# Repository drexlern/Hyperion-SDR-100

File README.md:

# Hyperion SDR-100

An open-source, homebrew **100W all-mode, all-band (160m–10m) HF Software-Defined Radio (SDR) transceiver** built around a **Xilinx Zynq SoC** architecture, an autonomous **7×7 L-network automatic antenna tuner (ATU)**, and a **60 FPS cross-platform desktop control head**.

---

## System Architecture

Hyperion SDR-100 is designed modularly so each RF, embedded, and software subsystem can be built, tested, and verified independently on the bench:

* **`/hardware-atu` — 100W 7×7 Automatic Antenna Tuner (KiCad):**
  * **Matching Network:** Binary-switched 7-inductor ($0.05\,\mu\text{H}$ – $4.5\,\mu\text{H}$ on Micrometals Type-2 powdered iron toroids) and 7-capacitor ($10\,\text{pF}$ – $1000\,\text{pF}$, $1\,\text{kV}$ C0G/NP0) L-network.
  * **Switching Matrix:** 16 Omron G2RL power relays ($14\times$ G2RL-1 SPDT for L/C banks, $1\times$ G2RL-2 DPDT for L/C topology reversal, $1\times$ G2RL-2 DPDT for full tuner bypass) driven via two daisy-chained **TI TPIC6B595N** open-drain shift registers.
  * **SWR & Power Sensing:** Built-in **Tandem Match (Stockton) directional coupler** wound on Fair-Rite BN43-202 binocular cores with 1N5711 Schottky peak detectors and $3.3\,\text{V}$ Zener ADC overvoltage protection.
  * **Controller:** **Seeed Studio XIAO ESP32-C3** mounted via through-hole headers for autonomous SWR tuning and USB/UART telemetry.
* **`/desktop-gui` — Shack Control Head (Python / Dear ImGui):**
  * 60 FPS OpenGL panadapter and 2D waterfall display powered by `imgui-bundle` (Dear ImGui + ImPlot) and `numpy`.
  * Live VFO tuning, band switching, real-time 16-relay ATU state visualizer, forward/reflected power & SWR metering, and a 180-second TX watchdog timer.
  * Designed for local Windows/Linux shack operation and low-latency remote streaming via **Parsec**.
* **`/firmware-esp32c3` — ATU Firmware (C++ / PlatformIO):** *(In Development)*
  * High-speed SPI shift-register control, ADC forward/reflected power sampling, and automated L/C impedance matching algorithms.
* **`/zynq-soc` — SDR Baseband & DSP (HDL / ARM C++):** *(Planned)*
  * Xilinx Zynq-7000 FPGA fabric for Digital Down/Up Conversion (DDC/DUC) and dual-core ARM Cortex-A9 processing system for rig control and Ethernet IQ/FFT streaming.

---

## Repository Structure

```text
Hyperion-SDR-100/
├── hardware-atu/        # KiCad schematics, PCB layouts, and custom footprints
├── desktop-gui/         # Python/ImGui transceiver control head and ATU dashboard
├── firmware-esp32c3/    # XIAO ESP32-C3 ATU controller firmware
├── zynq-soc/            # Xilinx Zynq SoC HDL and embedded C/C++ software
├── README.md            # Project overview and architecture
├── ATTRIBUTIONS.md      # Third-party hardware references, libraries, and licenses
└── LICENSE.md           # Dual open-source hardware and software license terms

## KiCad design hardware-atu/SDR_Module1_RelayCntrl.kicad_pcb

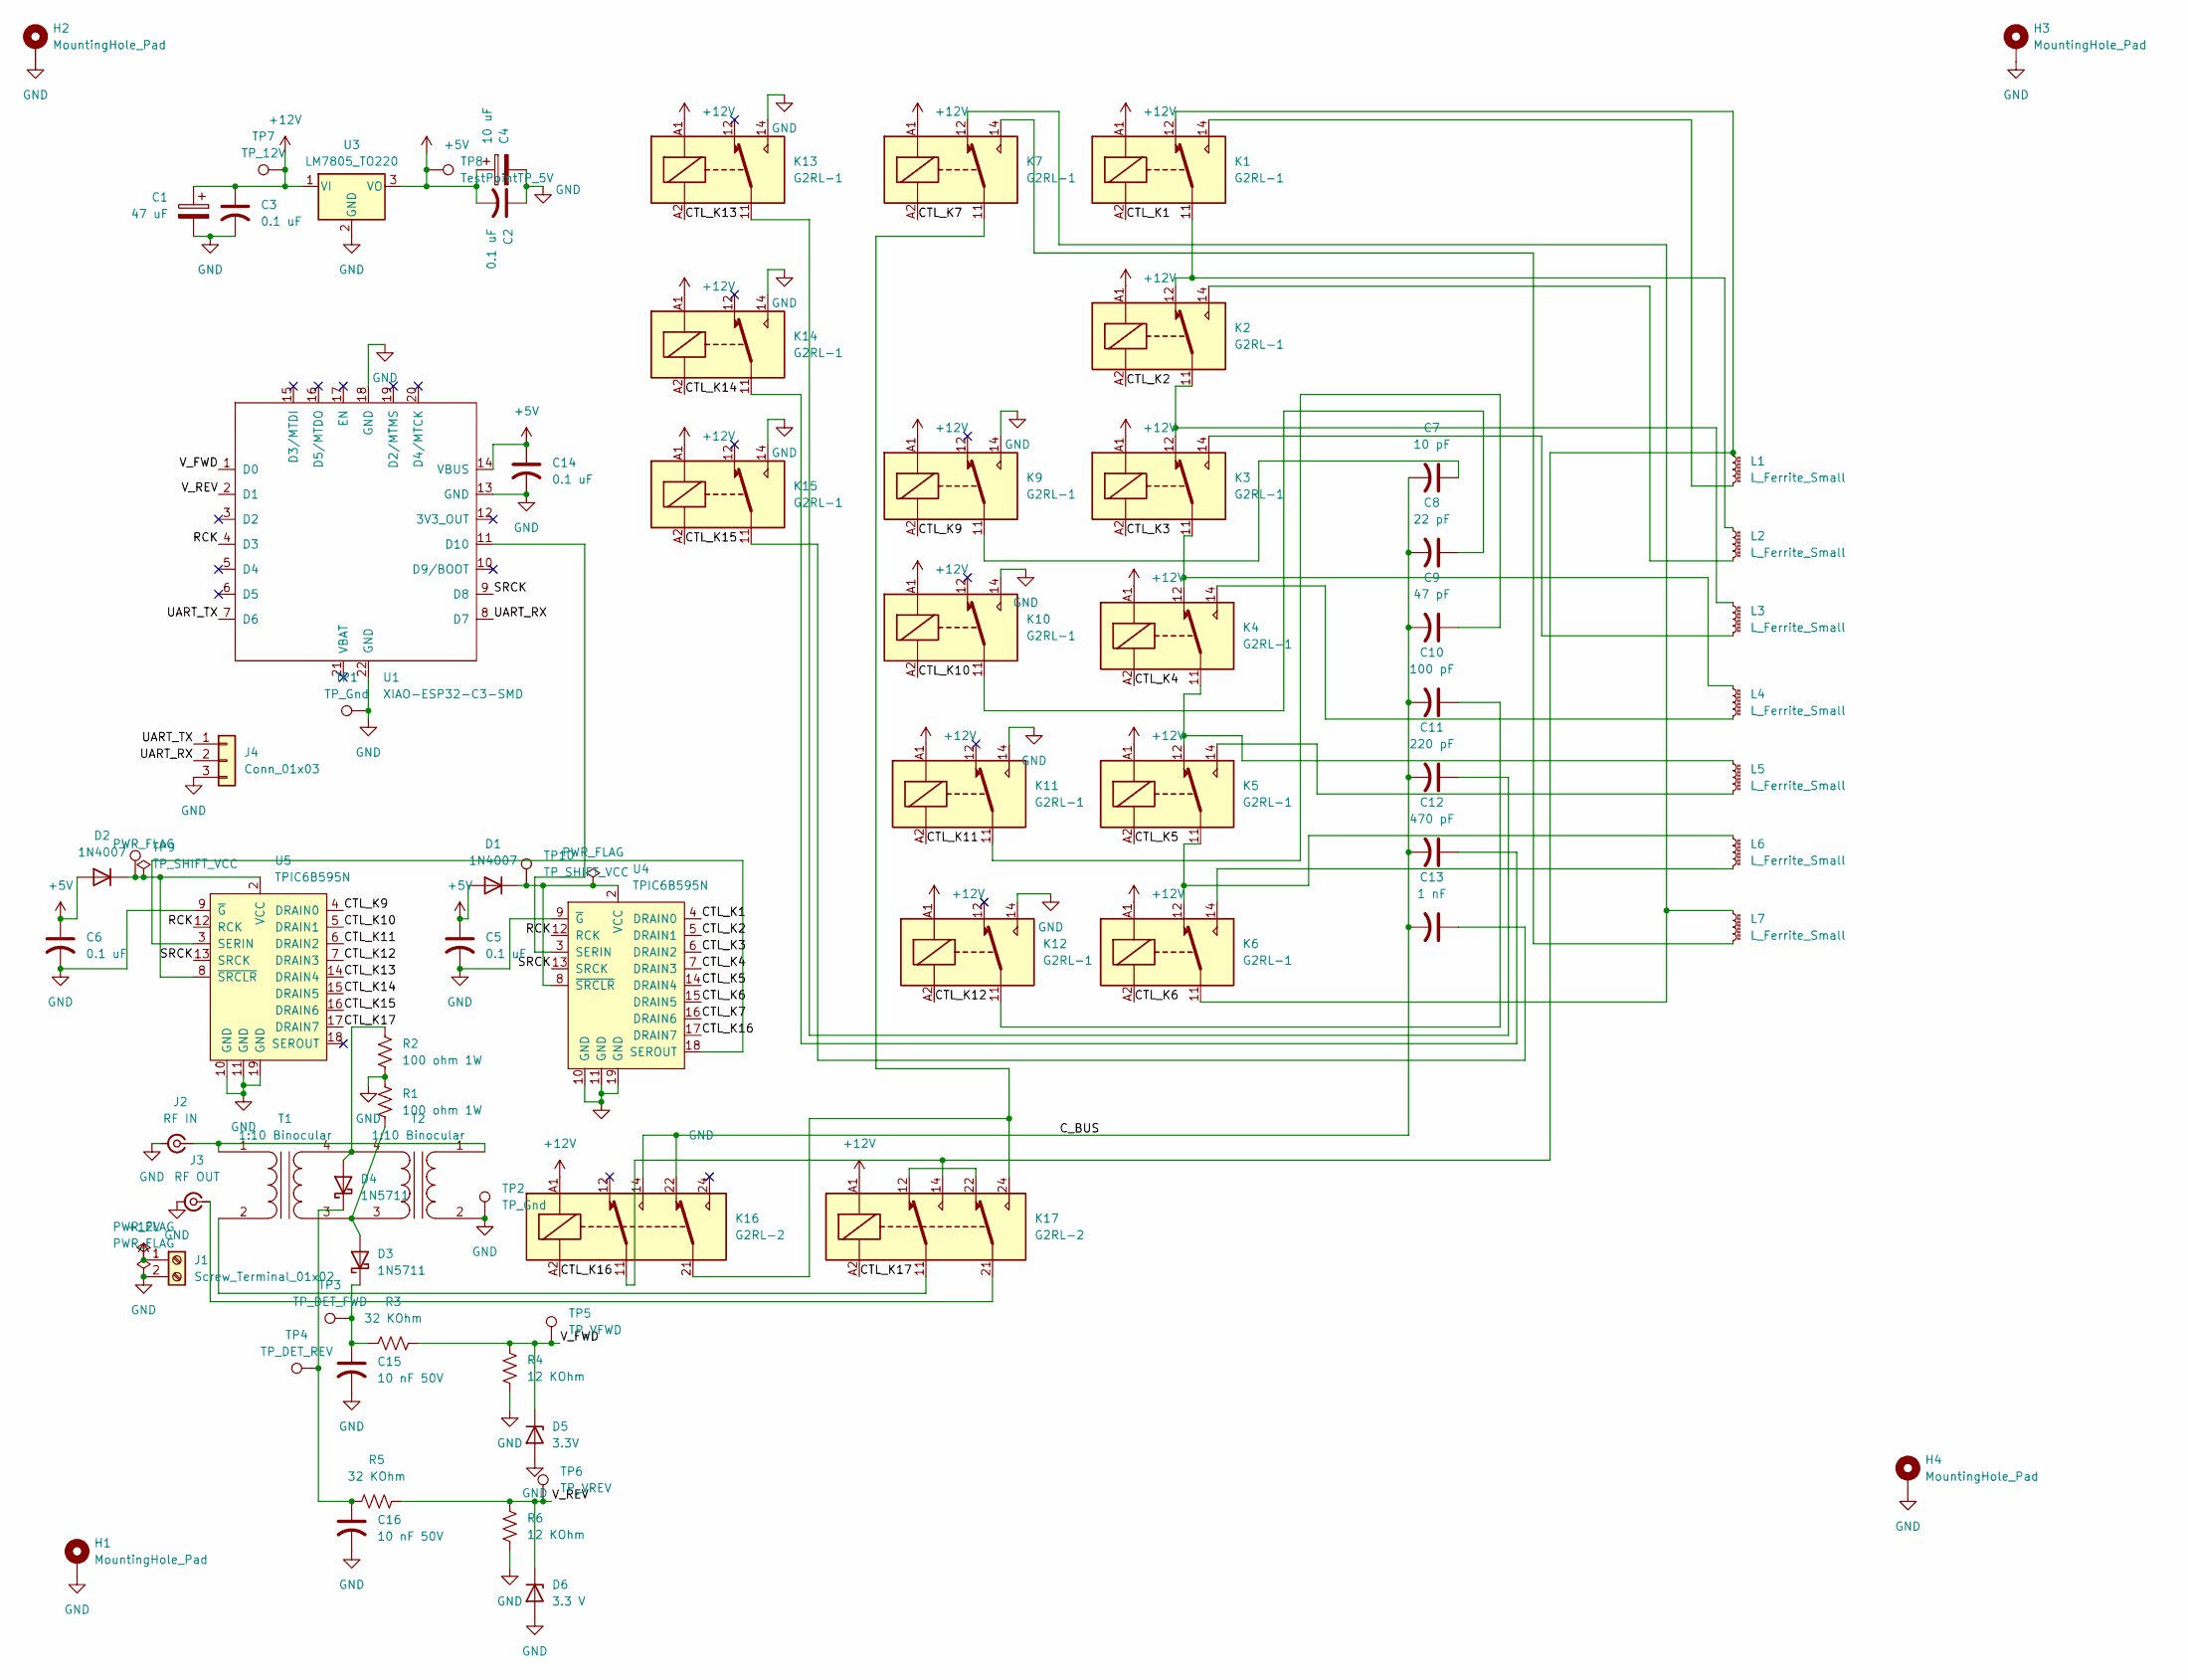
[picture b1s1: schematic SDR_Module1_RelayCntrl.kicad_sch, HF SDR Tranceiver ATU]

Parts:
C1: 47 uF; CP_Radial_D5.0mm_P2.00mm
C2, C3, C5, C6, C14: 0.1 uF; C_Rect_L4.0mm_W2.5mm_P2.50mm
C4: 10 uF; CP_Radial_D5.0mm_P2.00mm
C7: 10 pF; C_Disc_D7.5mm_W5.0mm_P5.00mm
C8: 22 pF; C_Disc_D7.5mm_W5.0mm_P5.00mm
C9: 47 pF; C_Disc_D7.5mm_W5.0mm_P5.00mm
C10: 100 pF; C_Disc_D7.5mm_W5.0mm_P5.00mm
C11: 220 pF; C_Disc_D7.5mm_W5.0mm_P5.00mm
C12: 470 pF; C_Disc_D7.5mm_W5.0mm_P5.00mm
C13: 1 nF; C_Disc_D10.5mm_W5.0mm_P5.00mm
C15, C16: 10 nF 50V; C_Disc_D5.0mm_W2.5mm_P5.00mm
D1, D2: 1N4007; D_DO-41_SOD81_P10.16mm_Horizontal
D3, D4: 1N5711; D_DO-35_SOD27_P7.62mm_Horizontal
D5: 3.3V; D_DO-35_SOD27_P7.62mm_Horizontal
D6: 3.3 V; D_DO-35_SOD27_P7.62mm_Horizontal
H1, H2, H3, H4: MountingHole_Pad; MountingHole_3.2mm_M3_Pad_Via
J1: Screw_Terminal_01x02; TerminalBlock_MetzConnect_Type175_RT02702HBLC_1x02_P7.50mm_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
J2: RF IN; SMA_Amphenol_132134_Vertical
J3: RF OUT; SMA_Amphenol_132134_Vertical
J4: Conn_01x03; JST_XH_B3B-XH-A_1x03_P2.50mm_Vertical
K1, K2, K3, K4, K5, K6, K7, K9, K10, K11, K12, K13, K14, K15: G2RL-1; Relay_SPDT_Omron_G2RL-1
K16, K17: G2RL-2; Relay_DPDT_Omron_G2RL-2
L1: L_Ferrite_Small; L_Axial_L12.0mm_D5.0mm_P15.24mm_Horizontal_Fastron_MISC
L2, L3, L4, L5, L6, L7: L_Ferrite_Small; Toroid_Vertical_T68_THT
R1, R2: 100 ohm 1W; R_Axial_DIN0411_L9.9mm_D3.6mm_P12.70mm_Horizontal
R3, R5: 32 KOhm; R_Axial_DIN0207_L6.3mm_D2.5mm_P10.16mm_Horizontal
R4, R6: 12 KOhm; R_Axial_DIN0207_L6.3mm_D2.5mm_P10.16mm_Horizontal
T1, T2: 1:10 Binocular; Transformer_BN43-202_THT
TP1, TP2: TP_Gnd; TestPoint_Loop_D2.50mm_Drill1.0mm
TP3: TP_DET_FWD; TestPoint_Loop_D2.50mm_Drill1.0mm
TP4: TP_DET_REV; TestPoint_Loop_D2.50mm_Drill1.0mm
TP5: TP_VFWD; TestPoint_Loop_D2.50mm_Drill1.0mm
TP6: TP_VREV; TestPoint_Loop_D2.50mm_Drill1.0mm
TP7: TP_12V; TestPoint_Pad_D2.0mm
TP8: TestPointTP_5V; TestPoint_Pad_D2.0mm
TP9, TP10: TP_SHIFT_VCC; TestPoint_Pad_D2.0mm
U1: XIAO-ESP32-C3-SMD; XIAO-ESP32-C3-DIP-SMD
U3: LM7805_TO220; TO-220-3_Vertical
U4, U5: TPIC6B595N; DIP-20_W7.62mm; Mouser Part Number 595-TPIC6B595N

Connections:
+5V: C2.2, C4.1, C5.1, C6.1, C14.1, D1.2 (A), D2.2 (A), TP8.1 (1_1), U1.14 (VBUS), U3.3 (VO)
+12V: C1.1, C3.1, J1.1, K1.A1, K2.A1, K3.A1, K4.A1, K5.A1, K6.A1, K7.A1, K9.A1, K10.A1, K11.A1, K12.A1, K13.A1, K14.A1, K15.A1, K16.A1, K17.A1, TP7.1 (1_1), U3.1 (VI)
/CTL_K1: K1.A2, U4.4 (DRAIN0)
/CTL_K2: K2.A2, U4.5 (DRAIN1)
/CTL_K3: K3.A2, U4.6 (DRAIN2)
/CTL_K4: K4.A2, U4.7 (DRAIN3)
/CTL_K5: K5.A2, U4.14 (DRAIN4)
/CTL_K6: K6.A2, U4.15 (DRAIN5)
/CTL_K7: K7.A2, U4.16 (DRAIN6)
/CTL_K9: K9.A2, U5.4 (DRAIN0)
/CTL_K10: K10.A2, U5.5 (DRAIN1)
/CTL_K11: K11.A2, U5.6 (DRAIN2)
/CTL_K12: K12.A2, U5.7 (DRAIN3)
/CTL_K13: K13.A2, U5.14 (DRAIN4)
/CTL_K14: K14.A2, U5.15 (DRAIN5)
/CTL_K15: K15.A2, U5.16 (DRAIN6)
/CTL_K16: K16.A2, U4.17 (DRAIN7)
/CTL_K17: K17.A2, U5.17 (DRAIN7)
/C_BUS: C7.2, C8.2, C9.2, C10.2, C11.2, C12.2, C13.2, K16.14, K16.22
/RCK: U1.4 (D3), U4.12 (RCK), U5.12 (RCK)
/SRCK: U1.9 (D8), U4.13 (SRCK), U5.13 (SRCK)
/UART_RX: J4.2, U1.8 (D7)
/UART_TX: J4.1, U1.7 (D6)
/V_FWD: D5.1 (K), R3.2, R4.1, TP5.1 (1_1), U1.1 (D0)
/V_REV: D6.1 (K), R5.2, R6.1, TP6.1 (1_1), U1.2 (D1)
GND: C1.2, C2.1, C3.2, C4.2, C5.2, C6.2, C14.2, C15.2, C16.2, D5.2 (A), D6.2 (A), H1.1 (1_1), H2.1 (1_1), H3.1 (1_1), H4.1 (1_1), J1.2, J2.2 (Ext), J3.2 (Ext), J4.3, K9.14, K10.14, K11.14, K12.14, K13.14, K14.14, K15.14, R1.1, R2.2, R4.2, R6.2, T2.2 (AB), TP1.1 (1_1), TP2.1 (1_1), U1.13 (GND), U1.18 (GND), U1.22 (GND), U3.2 (GND), U4.9 (~G), U4.10 (GND), U4.11 (GND), U4.19 (GND), U5.9 (~G), U5.10 (GND), U5.11 (GND), U5.19 (GND)
unnamed: C7.1, K9.11
unnamed: C8.1, K10.11
unnamed: C9.1, K11.11
unnamed: C10.1, K12.11
unnamed: C11.1, K13.11
unnamed: C12.1, K14.11
unnamed: C13.1, K15.11
unnamed: D1.1 (K), TP10.1 (1_1), U4.2 (VCC), U4.8 (~SRCLR)
unnamed: D2.1 (K), TP9.1 (1_1), U5.2 (VCC), U5.8 (~SRCLR)
unnamed: D3.2 (A), R1.2, T1.3 (SA), T2.3 (SA)
unnamed: C15.1, D3.1 (K), R3.1, TP3.1 (1_1)
unnamed: D4.2 (A), R2.1, T1.4 (SB), T2.4 (SB)
unnamed: C16.1, D4.1 (K), R5.1, TP4.1 (1_1)
unnamed: J2.1 (In), T1.1 (AA), T2.1 (AA)
unnamed: J3.1 (In), K17.21
unnamed: K1.11, K2.12, L2.1
unnamed: K1.12, K16.11, K17.14, L1.1
unnamed: K1.14, L1.2
unnamed: K2.11, K3.12, L3.1
unnamed: K2.14, L2.2
unnamed: K3.11, K4.12, L4.1
unnamed: K3.14, L3.2
unnamed: K4.11, K5.12, L5.1
unnamed: K4.14, L4.2
unnamed: K5.11, K6.12, L6.1
unnamed: K5.14, L5.2
unnamed: K6.11, K7.12, L7.1
unnamed: K6.14, L6.2
unnamed: K7.14, L7.2
unnamed: K7.11, K16.21, K17.24
unnamed: K17.12, K17.22
unnamed: K17.11, T1.2 (AB)
unnamed: U1.11 (D10), U4.3 (SERIN)
unnamed: U4.18 (SEROUT), U5.3 (SERIN)

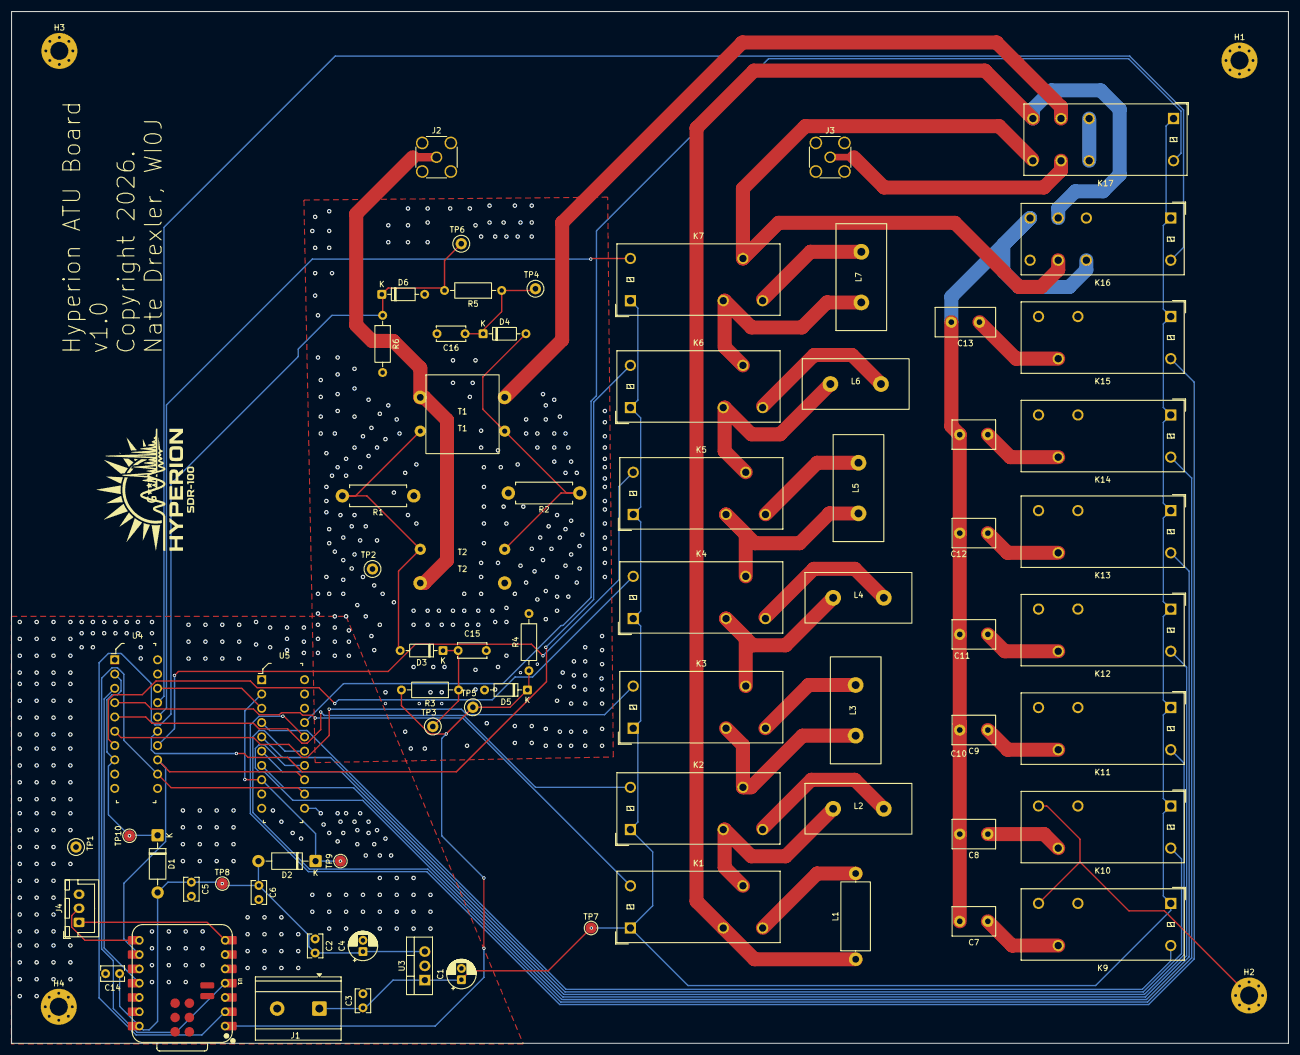
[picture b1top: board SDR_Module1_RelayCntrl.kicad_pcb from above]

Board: 2 copper layers, 227.0 x 183.4 mm, 75 parts (1 on the bottom side), 60 nets.

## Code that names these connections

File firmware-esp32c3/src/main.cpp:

#include <Arduino.h>
#include <SPI.h>
#include <math.h>

// ============================================================================
// 1. Verified Hardware Pin Definitions (Seeed Studio XIAO ESP32-C3)
// ============================================================================
constexpr uint8_t PIN_V_FWD  = D0;   // GPIO2 (ADC1_CH2) - Physical Pin 1
constexpr uint8_t PIN_V_REV  = D1;   // GPIO3 (ADC1_CH3) - Physical Pin 2
constexpr uint8_t PIN_RCK    = D3;   // GPIO5            - Physical Pin 4 -> U4/U5 Pin 12
constexpr uint8_t PIN_SRCK   = D8;   // GPIO8 (SPI SCK)  - Physical Pin 9 -> U4/U5 Pin 13
constexpr uint8_t PIN_SER_IN = D10;  // GPIO10 (MOSI)    - Physical Pin 11 -> U4 Pin 3

// ============================================================================
// 2. RF Coupler & Calibration Constants
// ============================================================================
constexpr float COUPLER_RATIO      = 10.0f;  // 10:1 BN-43-202 Tandem Match
constexpr float ADC_DIVIDER_RATIO  = 2.0f;   // 32.4k / 32.4k 2:1 divider (R3-R6)
constexpr float DIODE_DROP_V       = 0.25f;  // 1N5711 Schottky forward drop
constexpr float ADC_CAL_SCALE      = 1.00f;  // Trim against dummy load + wattmeter
constexpr float MIN_TUNE_POWER_W   = 3.0f;   // Minimum carrier power to sense SWR
constexpr float MAX_TUNE_POWER_W   = 25.0f;  // Protect G2RL contacts during switching
constexpr float TARGET_SWR         = 1.35f;  // Stop auto-tune once SWR <= 1.35:1
constexpr uint16_t RELAY_SETTLE_MS = 8;      // Omron G2RL operate/release (~5-7ms)

// ============================================================================
// 3. ATU State (Matches desktop-gui RadioState bitmasks)
//    U4: Bit 0..6 = L1..L7 (0.05uH..4.5uH), Bit 7 = K16 (0: C on ANT, 1: C on TX)
//    U5: Bit 0..6 = C1..C7 (10pF..1000pF),  Bit 7 = K17 (0: Bypass,   1: Active)
// ============================================================================
struct AtuState {
    uint8_t u4_l_mask = 0x00;
    uint8_t u5_c_mask = 0x00;
    float fwd_watts   = 0.0f;
    float ref_watts   = 0.0f;
    float swr         = 1.0f;
    bool tuning       = false;
};

AtuState atu;
uint32_t last_telemetry_ms = 0;

// ============================================================================
// 4. Shift Register Driver (U4 -> U5 Daisy-Chained TPIC6B595N)
// ============================================================================
void applyRelays(uint8_t u4_mask, uint8_t u5_mask) {
    atu.u4_l_mask = u4_mask;
    atu.u5_c_mask = u5_mask;

    SPI.beginTransaction(SPISettings(1000000, MSBFIRST, SPI_MODE0));
    digitalWrite(PIN_RCK, LOW);
    // U5 is downstream of U4 (U4 SER_OUT -> U5 SER_IN), so clock U5 out first
    SPI.transfer(u5_mask);
    SPI.transfer(u4_mask);
    digitalWrite(PIN_RCK, HIGH);
    SPI.endTransaction();

    delay(RELAY_SETTLE_MS);
}

// ============================================================================
// 5. Tandem Match SWR & Power Measurement
// ============================================================================
void measureSwr() {
    constexpr int SAMPLES = 32;
    uint32_t sum_fwd_mv = 0;
    uint32_t sum_ref_mv = 0;

    for (int i = 0; i < SAMPLES; i++) {
        sum_fwd_mv += analogReadMilliVolts(PIN_V_FWD);
        sum_ref_mv += analogReadMilliVolts(PIN_V_REV);
    }

    float v_fwd_adc = (sum_fwd_mv / (float)SAMPLES) / 1000.0f;
    float v_ref_adc = (sum_ref_mv / (float)SAMPLES) / 1000.0f;

    float v_fwd_peak = (v_fwd_adc > 0.015f)
        ? ((v_fwd_adc * ADC_DIVIDER_RATIO) + DIODE_DROP_V) * COUPLER_RATIO * ADC_CAL_SCALE
        : 0.0f;

    float v_ref_peak = (v_ref_adc > 0.015f)
        ? ((v_ref_adc * ADC_DIVIDER_RATIO) + DIODE_DROP_V) * COUPLER_RATIO * ADC_CAL_SCALE
        : 0.0f;

    atu.fwd_watts = (v_fwd_peak * v_fwd_peak) / 100.0f;
    atu.ref_watts = (v_ref_peak * v_ref_peak) / 100.0f;

    if (atu.fwd_watts < 0.2f) {
        atu.swr = 1.0f;
    } else {
        float rho = sqrtf(fminf(atu.ref_watts / atu.fwd_watts, 0.99f));
        atu.swr = (1.0f + rho) / fmaxf(1.0f - rho, 0.01f);
    }
}

// ============================================================================
// 6. Two-Pass Coarse + Fine Binary L/C Auto-Tune Algorithm
// ============================================================================
void runAutoTune() {
    measureSwr();
    if (atu.fwd_watts < MIN_TUNE_POWER_W) {
        Serial.println("ERR:LOW_PWR");
        return;
    }
    if (atu.fwd_watts > MAX_TUNE_POWER_W) {
        Serial.println("ERR:HIGH_PWR_PROTECT");
        return;
    }

    atu.tuning = true;
    float best_swr = 99.0f;
    uint8_t best_u4 = 0x00;
    uint8_t best_u5 = 0x80; // Bit 7 = 1 engages ATU (K17 active)

    // Pass 1: Coarse sweep across both topologies (K16: 0 = C on ANT, 1 = C on TX)
    for (uint8_t topo = 0; topo <= 1; topo++) {
        uint8_t topo_bit = (topo << 7);

        for (uint8_t l_val = 0; l_val < 128; l_val += 4) {
            for (uint8_t c_val = 0; c_val < 128; c_val += 4) {
                applyRelays(topo_bit | l_val, 0x80 | c_val);
                measureSwr();

                if (atu.fwd_watts < MIN_TUNE_POWER_W) {
                    atu.tuning = false;
                    applyRelays(best_u4, best_u5);
                    Serial.println("ERR:TX_DROPPED");
                    return;
                }

                if (atu.swr < best_swr) {
                    best_swr = atu.swr;
                    best_u4 = topo_bit | l_val;
                    best_u5 = 0x80 | c_val;
                }
                if (best_swr <= TARGET_SWR) break;
            }
            if (best_swr <= TARGET_SWR) break;
        }
        if (best_swr <= TARGET_SWR) break;
    }

    // Pass 2: Fine-tune +/- 3 steps around best coarse L and C values
    uint8_t base_topo = best_u4 & 0x80;
    int base_l = best_u4 & 0x7F;
    int base_c = best_u5 & 0x7F;

    for (int dl = -3; dl <= 3; dl++) {
        int l_try = constrain(base_l + dl, 0, 127);
        for (int dc = -3; dc <= 3; dc++) {
            int c_try = constrain(base_c + dc, 0, 127);
            applyRelays(base_topo | (uint8_t)l_try, 0x80 | (uint8_t)c_try);
            measureSwr();

            if (atu.fwd_watts < MIN_TUNE_POWER_W) {
                atu.tuning = false;
                applyRelays(best_u4, best_u5);
                Serial.println("ERR:TX_DROPPED");
                return;
            }

            if (atu.swr < best_swr) {
                best_swr = atu.swr;
                best_u4 = base_topo | (uint8_t)l_try;
                best_u5 = 0x80 | (uint8_t)c_try;
            }
        }
    }

    applyRelays(best_u4, best_u5);
    atu.tuning = false;
    Serial.printf("TUNED:U4=%02X,U5=%02X,SWR=%.2f\n", best_u4, best_u5, best_swr);
}

// ============================================================================
// 7. Serial Command Handler (Matches desktop-gui atu_serial.py)
// ============================================================================
void handleSerialCommands() {
    if (!Serial.available()) return;

    String cmd = Serial.readStringUntil('\n');
    cmd.trim();
    cmd.toUpperCase();

    if (cmd.startsWith("SET ")) {
        unsigned int u4 = 0, u5 = 0;
        if (sscanf(cmd.c_str() + 4, "%x %x", &u4, &u5) == 2) {
            applyRelays((uint8_t)u4, (uint8_t)u5);
            Serial.printf("ACK:SET,%02X,%02X\n", atu.u4_l_mask, atu.u5_c_mask);
        }
    } else if (cmd == "TUNE") {
        runAutoTune();
    } else if (cmd == "BYPASS") {
        applyRelays(0x00, 0x00);
        Serial.println("ACK:BYPASS");
    } else if (cmd == "PING") {
        Serial.println("PONG:HYPERION_ATU_V1");
    }
}

void setup() {
    Serial.begin(115200);
    analogReadResolution(12);
    analogSetAttenuation(ADC_11db);

    pinMode(PIN_RCK, OUTPUT);
    digitalWrite(PIN_RCK, LOW);

    SPI.begin(PIN_SRCK, -1, PIN_SER_IN, PIN_RCK);
    applyRelays(0x00, 0x00); // Safe power-up state: full tuner bypass
}

void loop() {
    handleSerialCommands();

    // Stream live telemetry at 20 Hz (every 50 ms) to desktop-gui
    uint32_t now = millis();
    if (now - last_telemetry_ms >= 50) {
        last_telemetry_ms = now;
        measureSwr();
        Serial.printf("TEL:%.1f,%.1f,%.2f,%02X,%02X,%d\n",
                      atu.fwd_watts,
                      atu.ref_watts,
                      atu.swr,
                      atu.u4_l_mask,
                      atu.u5_c_mask,
                      atu.tuning ? 1 : 0);
    }
}

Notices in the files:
hardware-atu/SDR_Module1_RelayCntrl.kicad_pcb:
Copyright 2026.
